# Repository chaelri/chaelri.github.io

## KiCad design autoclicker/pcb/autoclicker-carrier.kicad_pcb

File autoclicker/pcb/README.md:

# AutoClicker Carrier PCB v1.0

A 40 × 25 mm carrier board that takes the breadboard rats-nest off the bench and turns the ESP32-C3 SuperMini + MG90S servo into a clean, screw-mountable module.

## What it does

- Sockets the ESP32-C3 SuperMini on two 1×8 female header strips (no soldering of the module — pull it off any time)
- Routes 5V / GND / GPIO3 through copper traces to a 3-pin JST-PH connector for the MG90S pigtail
- Holds a 470 µF electrolytic across the 5V rail to absorb servo inrush spikes
- Lights a small red status LED whenever the board is powered
- Drops into any enclosure via four M2 mounting holes

USB-C lives on the SuperMini itself — it pokes off the LEFT short edge of the carrier so you can plug a powerbank straight in.

## Dimensions

| Item                  | Value                          |
|-----------------------|--------------------------------|
| Outline               | 40.0 × 25.0 mm                 |
| Thickness             | 1.6 mm (standard FR-4)         |
| Layers                | 2                              |
| Mounting holes        | 4 × Ø 2.2 mm (M2), 3 mm inset  |
| Header pitch          | 2.54 mm                        |
| Header row spacing    | 17.78 mm (0.7", SuperMini std) |
| Servo connector       | JST-PH 3-pin, 2.0 mm pitch     |
| Cap pad pitch         | 5.0 mm                         |

## Bill of materials

| Ref | Qty | Part                                    | Notes                          | ~₱ each |
|-----|-----|-----------------------------------------|--------------------------------|---------|
| —   | 1   | Bare PCB                                | JLCPCB 40×25 mm, 2-layer       | ~22 (5-pack ≈ ₱110) |
| J1  | 1   | 1×8 female header, 2.54 mm × 2          | Sockets the SuperMini          | 10      |
| J2  | 1   | JST-PH 3-pin vertical header            | For MG90S pigtail              | 15      |
| C1  | 1   | 470 µF / 16 V electrolytic, 5 mm pitch  | Servo bulk decoupling          | 5       |
| D1  | 1   | 5 mm red LED                            | Power indicator                | 2       |
| R1  | 1   | 330 Ω 1/4 W resistor                    | LED current limit              | 1       |
| —   | 4   | M2 × 6 mm machine screw + nut           | Optional, for enclosure        | 8 set   |

Total **~₱65** in components per board, plus the shared PCB cost. SuperMini and servo come from the existing build.

## Schematic (textual)

```
  [USB-C 5V] ─┬─ ESP32-C3 5V ───┬───── J2 pin 1 (5V, red wire)
              │                 ├──[+] C1 [−]── ESP32-C3 GND
              └──── R1 ── D1[A] D1[K] ── ESP32-C3 GND
  ESP32-C3 GND ─────────────────┴───── J2 pin 3 (GND, brown wire)
  ESP32-C3 GPIO3 ────────────────────  J2 pin 2 (SIG, orange/yellow wire)
```

Three signal nets total. No transistor, no MOSFET, no flyback diode — the servo is a non-inductive load (from the firmware's perspective; the gear motor's brushes are inside the servo's own controller).

## Manufacturing

### Option A — JLCPCB (recommended starting point)

1. Open `autoclicker-carrier.svg` in [KiCad PcbNew](https://www.kicad.org/) → **File ▸ Import ▸ Graphics**, scale 1.0, layer `Edge.Cuts` for the outline + `F.SilkS` for labels.
2. Place footprints from the standard libraries:
   - `Connector_PinHeader_2.54mm:PinHeader_1x08_P2.54mm_Vertical` × 2
   - `Connector_JST:JST_PH_S3B-PH-K_1x03_P2.00mm_Horizontal`
   - `Capacitor_THT:CP_Radial_D8.0mm_P5.00mm`
   - `LED_THT:LED_D5.0mm`
   - `Resistor_THT:R_Axial_DIN0207_L6.3mm_D2.5mm_P2.54mm_Vertical`
   - `MountingHole:MountingHole_2.2mm_M2`
3. Route the three traces shown above on the **top** copper layer (default 0.4 mm trace width is fine for ~1 A).
4. Pour a GND fill on the bottom layer and stitch with a few vias for thermal mass.
5. **File ▸ Plot** → Gerbers + drill files (Excellon, metric, decimal). Zip them.
6. Upload to JLCPCB. Defaults are correct for this design: 1.6 mm FR-4, HASL lead-free, 2 layers, green soldermask, white silkscreen. Order qty 5 — minimum is cheaper than qty 1.

### Option B — toner transfer / hand-etched

The design is simple enough (3 nets) that a hand-routed single-sided board works. Mirror the SVG, print on glossy paper, transfer with a hot iron onto copper-clad, etch with ferric chloride. Drill with a 1.0 mm bit for the through-holes and 2.2 mm for mounting.

## Assembly

1. Solder the two 1×8 female headers first — flip the board upside-down on a flat surface with the headers in place to ensure they sit perpendicular.
2. Solder J2 (JST-PH), watching polarity against the silkscreen.
3. Solder C1 with the **long lead in the `+` pad** (left side, near the trace from 5V). Cap polarity is critical — backwards = bulging cap.
4. Solder R1 (any direction) and D1 (long lead = anode = `+` end, marked on silk).
5. Plug the SuperMini onto the headers. USB-C should poke off the left short edge.
6. Plug the MG90S pigtail onto J2. Check the wire colors against the silkscreen: red (5V) → pin 1, orange/yellow (signal) → pin 2, brown (GND) → pin 3. **MG90S pin order can differ between clones — always verify against the silkscreen, not your last build.**

## File map

```
pcb/
├── autoclicker-carrier.kicad_pro   ← KiCad project file (open this one in KiCad)
├── autoclicker-carrier.kicad_pcb   ← Board layout — opens in PcbNew
├── autoclicker-carrier.svg         ← 1:1 reference drawing (Inkscape / browser)
└── README.md                       ← this document
```

### Opening in KiCad

1. Install [KiCad 8 or later](https://www.kicad.org/download/) (free, cross-platform).
2. Open KiCad. **File ▸ Open Project** → pick `autoclicker-carrier.kicad_pro`.
3. From the project window, double-click the PCB file (or click the green **PCB Editor** button) to open the board in PcbNew. You'll see:
   - 40 × 25 mm board outline on `Edge.Cuts`
   - 4 mounting holes (M2, NPTH)
   - 2 socket strips for the SuperMini (J1 with the 5V/GND/SIG nets assigned, J2 as passthrough)
   - JST-PH 3-pin servo connector (J3)
   - 470 µF cap (C1), 5 mm LED (D1), 330 Ω resistor (R1)
   - Pre-routed copper: +5V / SIG / LED_A on **F.Cu** (top), GND on **B.Cu** (bottom)
   - Silkscreen labels: AUTOCLICKER, v1.0, pin labels at the JST, USB-C arrow, GPIO3 callout
4. Run **Inspect ▸ Design Rules Checker** — should pass with default DRC. If anything trips, the most likely cause is footprint clearances tighter than the global 0.2 mm clearance.
5. **File ▸ Plot…** to export Gerbers (defaults are fine — turn on `F.Cu / B.Cu / F.SilkS / F.Mask / B.Mask / Edge.Cuts`). Then **Generate Drill Files…** for the Excellon `.drl`. Zip everything in `gerber/` and upload to JLCPCB.

### Note on embedded footprints

The footprints (`Custom:PinSocket_1x08_Horizontal`, etc.) are **embedded in the .kicad_pcb file** — they don't reference any external library, so they'll resolve cleanly even on a fresh KiCad install with no extra libraries downloaded. The standard libraries (`MountingHole`, `Connector_JST`, `Capacitor_THT`, `LED_THT`, `Resistor_THT`) are also referenced for the parts that match KiCad's defaults; if you don't have them installed (highly unusual), KiCad will fall back to the embedded copies.

### No schematic — that's intentional

This is a board-only project (no `.kicad_sch`). The netlist is defined directly via pad net assignments in the PCB file. To add a schematic later: **File ▸ New ▸ Schematic**, draw the symbols, and run **Tools ▸ Update PCB from Schematic** to sync.

The SVG (`autoclicker-carrier.svg`) is a reference drawing — useful as an Inkscape source for graphics or as a printable 1:1 template, but it's not what you fab from. Always generate Gerbers from KiCad.

## Status

Designed but not yet manufactured. v1.0 is a paper design. Once a batch is fabbed and assembled, this file will be updated with errata.

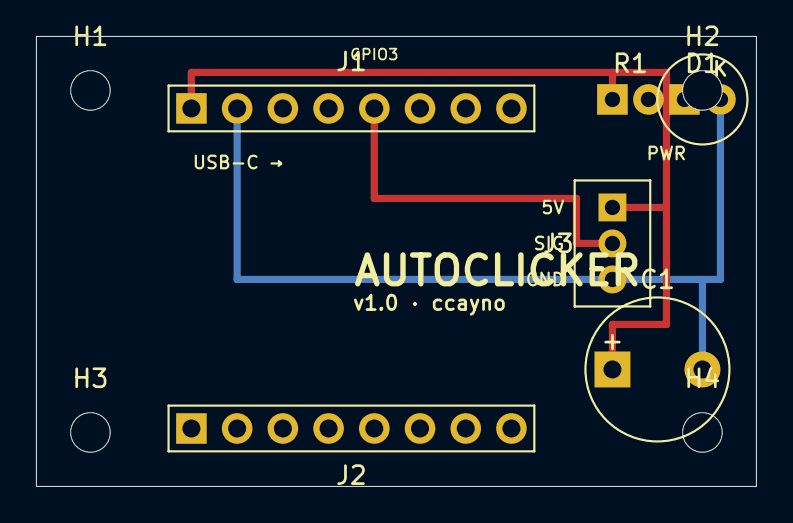
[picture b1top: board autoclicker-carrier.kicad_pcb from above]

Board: 2 copper layers, 40.0 x 25.0 mm, 10 parts (0 on the bottom side), 4 nets.

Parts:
C1: 470µF/16V; CP_Radial_D8.0mm_P5.00mm
D1: RED; LED_D5.0mm
H1, H2, H3, H4: M2; MountingHole_2.2mm_M2
J1: SuperMini top; PinSocket_1x08_Horizontal
J2: SuperMini bot; PinSocket_1x08_Horizontal
J3: Servo; JST_PH_S3B-PH-K_1x03_P2.00mm_Vertical
R1: 330Ω; R_Axial_DIN0207_L6.3mm_D2.5mm_P2.54mm_Vertical

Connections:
+5V: C1.1, J1.1, J3.1, R1.1
GND: C1.2, D1.2, J1.2, J3.3
LED_A: D1.1, R1.2
SIG: J1.5, J3.2
